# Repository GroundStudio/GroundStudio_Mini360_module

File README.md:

GroundStudio Mini360 module
====================================

Get it from [ardushop.ro](https://ardushop.ro/ro/home/1732-modul-coborare-tensiune-mini360.html)

Explore all the GroundStudio products at [GroundStudio.ro](https://groundstudio.ro/)

Description
-------------------
Step down module based on AX3484 chip.

Contents
-------------------

* [/Documentation](https://github.com/GroundStudio/GroundStudio_Mini360_module/tree/main/Documentation) -- Contains documentation written during creation of this repository, with readme.md index of its own!
* [/Firmware](https://github.com/GroundStudio/GroundStudio_Mini360_module/tree/main/Firmware) -- Firmware (bootloaders, etc)
* [/Hardware](https://github.com/GroundStudio/GroundStudio_Mini360_module/tree/main/Hardware) -- Schematics, layout.
* [/Libraries](https://github.com/GroundStudio/GroundStudio_Mini360_module/tree/main/Libraries) -- Arduino/CircuitPython libraries. 
* [/Tools](https://github.com/GroundStudio/GroundStudio_Mini360_module/tree/main) -- Tools needed for compiling, uploading bootloader, etc.

Versions
-------------------
*(Not all tags shown)*
* [V0.2] Initial version

License
-------------------

This is released under the [Attribution-ShareAlike 4.0 International (CC BY-SA 4.0)](https://creativecommons.org/licenses/by-sa/4.0/) license. 
**You are welcome to use this for commercial purposes.**

Please consider contributing back to this project or others to help the open-source hardware community continue to thrive and grow! 

Certifications:

[Open Source Hardware Association](https://certification.oshwa.org/ro000012.html)   
   
[
](https://certification.oshwa.org/ro000012.html)

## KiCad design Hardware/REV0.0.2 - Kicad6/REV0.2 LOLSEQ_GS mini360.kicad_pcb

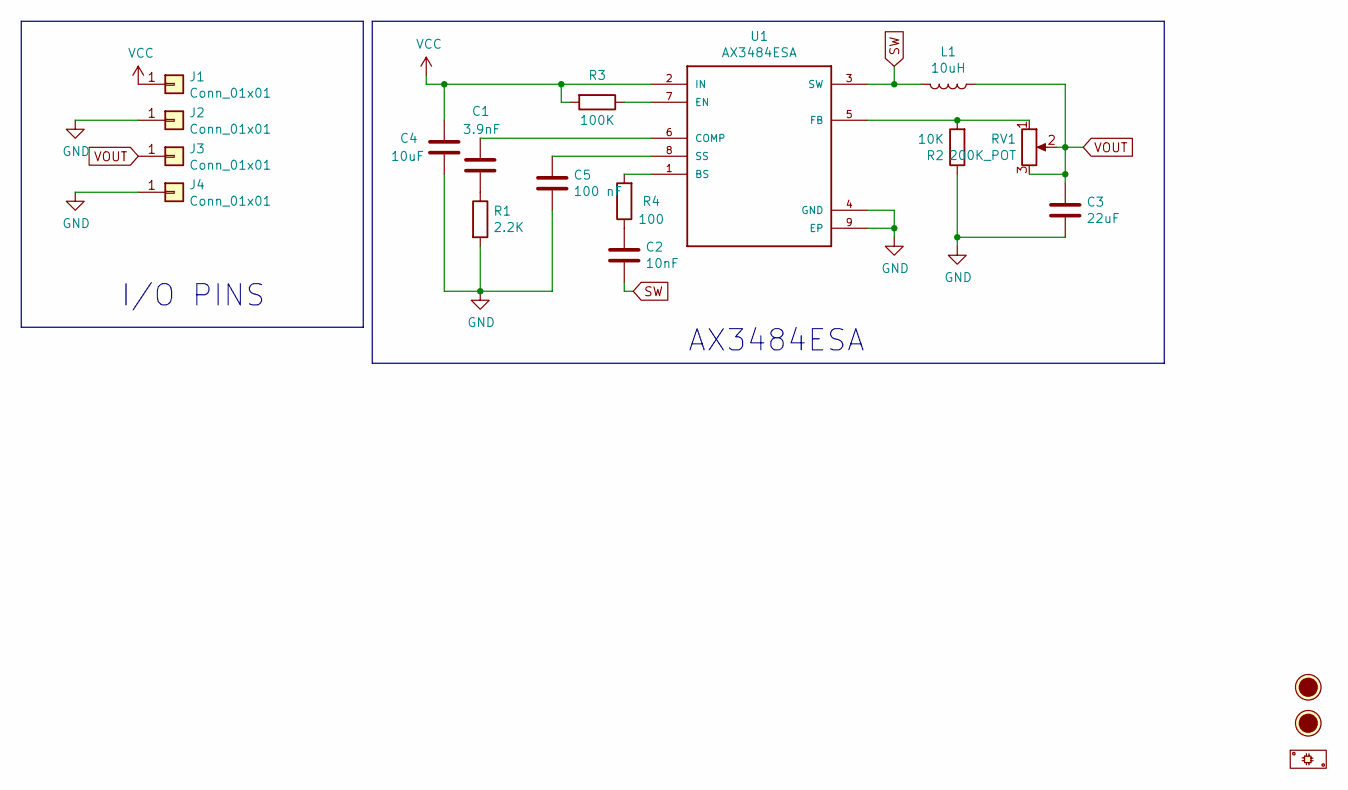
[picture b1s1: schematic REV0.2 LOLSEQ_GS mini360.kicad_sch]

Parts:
C1: 3.9nF; C_0603_1608Metric; MPN 0603B392K500NT; LCSC C1618
C2: 10nF; C_0402_1005Metric; MPN V103K0402X7R500NBT; LCSC C513436
C3: 22uF; C_0805_2012Metric; MPN C2012X5R1V226MT000E; LCSC C338080
C4: 10uF; C_1206_3216Metric; MPN CL31B106KAHNNNE; LCSC C14860
C5: 100 nF; C_0603_1608Metric; MPN 0603B104K160CT; LCSC C80516
FID1, FID2: Fiducial; Fiducial_0.75mm_Mask1.5mm
J1, J2, J3, J4: Conn_01x01; PinHeader_1x01_P2.54mm_Vertical_Male
L1: 10uH; MCS_0603; MPN MCS0630-100MN1; LCSC C385254
P1: PCB; MPN LOLSEQ_GS_PCB
R1: 2.2K; R_0402_1005Metric; MPN RC-02W2201FT; LCSC C258093
R2: 10K; R_0402_1005Metric; MPN 0402WGJ0103TCE; LCSC C25531
R3: 100K; R_0402_1005Metric; MPN 0402WGF1003TCE; LCSC C25741
R4: 100; R_0402_1005Metric; MPN WR04X1000FTL; LCSC C163808
RV1: 200K_POT; 35WR; MPN VG039NCHXTB204; LCSC C128551
U1: AX3484ESA; SOIC-8-1EP_3.9x4.9mm_P1.27mm_EP2.514x3.2mm; MPN AX3484ESA; LCSC C211632

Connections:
GND: C3.2, C4.2, C5.2, J2.1, J4.1, R1.2, R2.1, U1.4 (GND), U1.9 (EP)
unnamed: C1.1, U1.6 (COMP)
unnamed: C1.2, R1.1
unnamed: C2.1, R4.1
unnamed: C5.1, U1.8 (SS)
unnamed: R2.2, RV1.1, U1.5 (FB)
unnamed: R3.1, U1.7 (EN)
unnamed: R4.2, U1.1 (BS)
SW: C2.2, L1.2, U1.3 (SW)
VCC: C4.1, J1.1, R3.2, U1.2 (IN)
VOUT: C3.1, J3.1, L1.1, RV1.2, RV1.3

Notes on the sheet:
I/O PINS
AX3484ESA

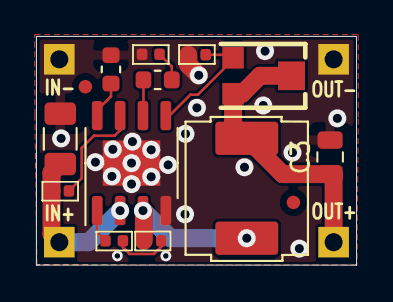
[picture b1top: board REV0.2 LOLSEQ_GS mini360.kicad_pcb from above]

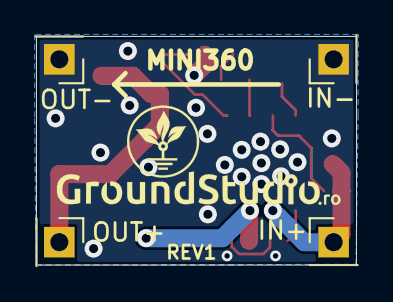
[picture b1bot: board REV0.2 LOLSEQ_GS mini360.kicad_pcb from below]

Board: 2 copper layers, 17.8 x 12.7 mm, 18 parts (4 on the bottom side), 11 nets.

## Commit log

2023-10-24 - first commit
2023-11-03 - added datasheet
